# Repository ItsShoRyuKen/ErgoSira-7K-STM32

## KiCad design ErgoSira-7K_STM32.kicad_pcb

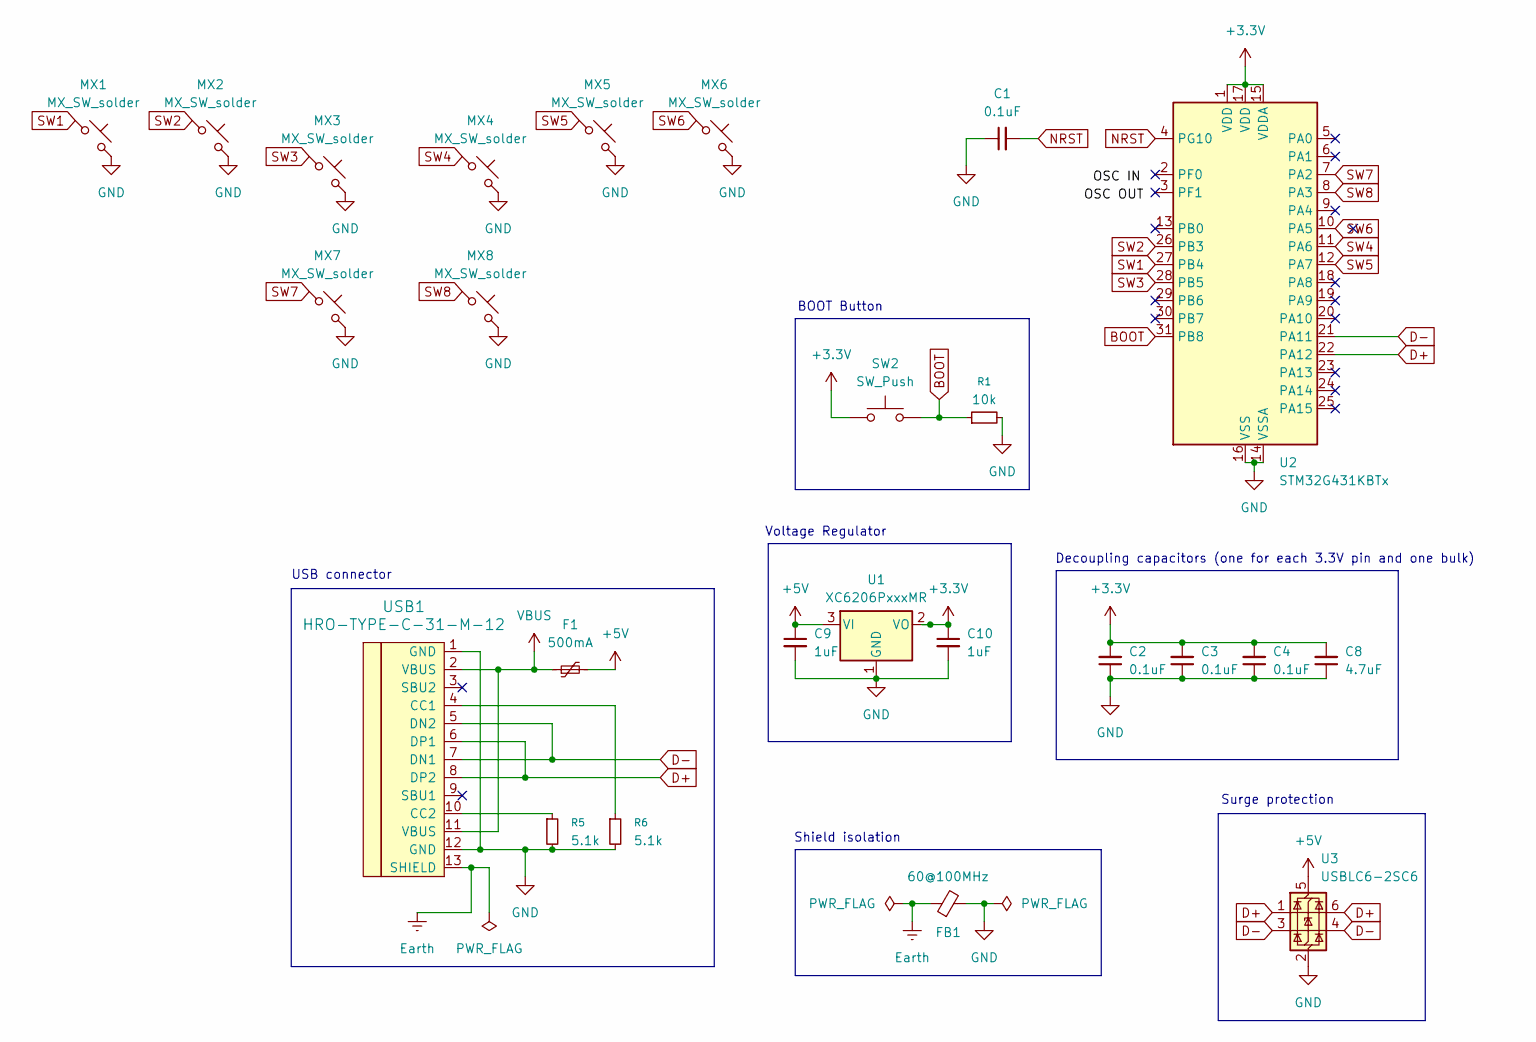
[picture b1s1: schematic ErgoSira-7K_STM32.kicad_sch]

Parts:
C1, C2, C3, C4: 0.1uF; C_0805_2012Metric_Pad1.18x1.45mm_HandSolder
C8: 4.7uF; C_0805_2012Metric_Pad1.18x1.45mm_HandSolder
C9, C10: 1uF; C_0805_2012Metric_Pad1.18x1.45mm_HandSolder
F1: 500mA; Fuse_1206_3216Metric_Pad1.42x1.75mm_HandSolder
FB1: 60@100MHz; L_0805_2012Metric_Pad1.05x1.20mm_HandSolder
MX1, MX2, MX3, MX4, MX5, MX6, MX7, MX8: MX_SW_solder; SW_MX_1u
R1: 10k; R_0805_2012Metric_Pad1.20x1.40mm_HandSolder
R5, R6: 5.1k; R_0805_2012Metric_Pad1.20x1.40mm_HandSolder
SW2: SW_Push; SW_SPST_SKQG_WithStem
U1: XC6206PxxxMR; SOT-23-3
U2: STM32G431KBTx; LQFP-32_7x7mm_P0.8mm
U3: USBLC6-2SC6; SOT-23-6
USB1: HRO-TYPE-C-31-M-12; HRO-TYPE-C-31-M-12-HandSoldering

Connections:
+3.3V: C2.2, C3.2, C4.2, C8.2, C10.1, SW2.1, U1.2 (VO), U2.1 (VDD), U2.15 (VDDA), U2.17 (VDD)
+5V: C9.1, F1.2, U1.3 (VI), U3.5 (VBUS)
BOOT: R1.1, SW2.2, U2.31 (PB8)
D+: U2.22 (PA12), U3.1 (I/O1), U3.6 (I/O1), USB1.6 (DP1), USB1.8 (DP2)
D-: U2.21 (PA11), U3.3 (I/O2), U3.4 (I/O2), USB1.5 (DN2), USB1.7 (DN1)
Earth: FB1.1, USB1.13 (SHIELD)
GND: C1.1, C2.1, C3.1, C4.1, C8.1, C9.2, C10.2, FB1.2, MX1.2, MX2.2, MX3.2, MX4.2, MX5.2, MX6.2, MX7.2, MX8.2, R1.2, R5.2, R6.2, U1.1 (GND), U2.14 (VSSA), U2.16 (VSS), U2.32 (VSS), U3.2 (GND), USB1.1 (GND), USB1.12 (GND)
NRST: C1.2, U2.4 (PG10)
unnamed: R6.1, USB1.4 (CC1)
unnamed: R5.1, USB1.10 (CC2)
SW1: MX1.1, U2.27 (PB4)
SW2: MX2.1, U2.26 (PB3)
SW3: MX3.1, U2.28 (PB5)
SW4: MX4.1, U2.11 (PA6)
SW5: MX5.1, U2.12 (PA7)
SW6: MX6.1, U2.10 (PA5)
SW7: MX7.1, U2.7 (PA2)
SW8: MX8.1, U2.8 (PA3)
VBUS: F1.1, USB1.2 (VBUS), USB1.11 (VBUS)

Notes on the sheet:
Surge protection
Decoupling capacitors (one for each 3.3V pin and one bulk)
Voltage Regulator
USB connector
Shield isolation
BOOT Button

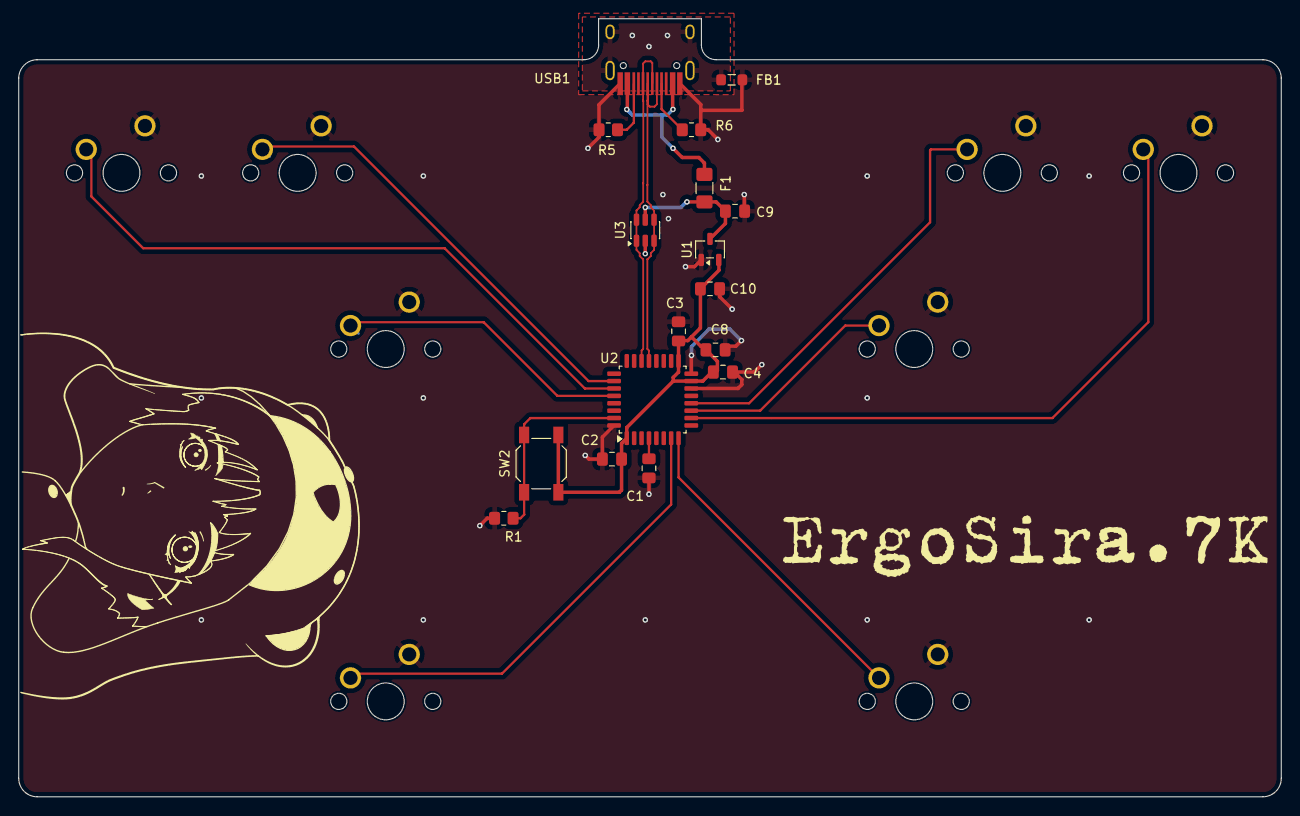
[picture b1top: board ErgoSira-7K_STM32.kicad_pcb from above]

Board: 2 copper layers, 136.5 x 84.1 mm, 25 parts (0 on the bottom side), 19 nets.

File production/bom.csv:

Designator,Footprint,Quantity,Value,LCSC Part #
"C1, C2, C3, C4",0805,4,0.1uF,
"C10, C9",0805,2,1uF,
C8,0805,1,4.7uF,
F1,1206,1,500mA,
FB1,0805,1,60@100MHz,
"MX1, MX2, MX3, MX4, MX5, MX6, MX7",SW_MX_1u,7,MX_SW_solder,
R1,0805,1,10k,
"R5, R6",0805,2,5.1k,
S1,STAB_MX_6.25u,1,MX_stab,
SW2,SW_SPST_SKQG_WithStem,1,SW_Push,
U1,SOT-23-3,1,XC6206PxxxMR,
U2,LQFP-32_7x7mm_P0.8mm,1,STM32G431KBTx,
U3,SOT-23-6,1,USBLC6-2SC6,
USB1,HRO-TYPE-C-31-M-12-HandSoldering,1,HRO-TYPE-C-31-M-12,

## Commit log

2026-01-06 added files
2026-01-07 changed usb footprint 3d model
2026-01-07 fixed stabilizers orientation. added graphics
2026-01-07 3d models
